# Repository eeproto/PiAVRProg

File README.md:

# Standalone AVR Programmer
Raspberry Pi based standalone ZIF Socket AVR Programmer

Program AVR chips with one click of a button:

Project Home Page: [https://eeproto.com/portfolio/avr-programmer/](https://eeproto.com/portfolio/avr-programmer/)

# Purpose

You designed a piece of hardware around an [AVR](https://en.wikipedia.org/wiki/AVR_microcontrollers) microcontroller, maybe the popular [ATmega328](https://www.microchip.com/wwwproducts/en/ATmega328). I love this powerful and inexpensive chip. Many projects use it, maybe because it is also the core of the even more popular [Arduino UNO](https://www.arduino.cc/en/Guide/ArduinoUno).

If you produce your new design two or three times, you flash your AVRs straight from your workstation. If you make 1,000, your distributor will gladly flash them for you. But what if you want, say, 50?

This project gives you all the parts to make a standalone, easy to use AVR programmer. It is Open Source, released under [Creative Commons Attribution-ShareAlike 4.0 International License](http://creativecommons.org/licenses/by-sa/4.0/), and it borrows from many other Open Source designs, including Sparkfun's [Pi AVR Programmer HAT](https://www.sparkfun.com/products/14747).

Hardware and software were tested with ATmega168 and ATmega328 chips. Feel free to adapt it to other AVR chips that support SPI programming.

# Make It

To make your own, get a Rasperry Pi. Any version should work, I tested it with a Pi 2 Model B v.1.1.

Make the custom PCB that connects the AVR socket, buttons, LEDs, etc. to the Pi.

Use the [KiCad](https://www.kicad-pcb.org/) project in the `hardware` folder to order your board. I got some from a low-cost PCB shop along with a stencil. It is a two-layer board with surface mount components on one side. There is a set of Gerber and drill files in the `hardware/plots` folder. The BOM in the same folder uses pretty generic components. The [octopart BOM](https://octopart.com/bom-tool/K1k6iRbx) might still be up.

Populate the surface mount components first. I use solder past, a stencil, tweezers, and a [ReflowR](http://www.reflowr.com/index.html) by [Lafras H](https://www.tindie.com/stores/LafrasH/). There are many other ways to do that, including hand soldering or reflowing with hot air like in this [EEVblog video](https://www.youtube.com/watch).

The 28 pin ZIF sockets can be a little hard to get, the major distributors might not have them in stock. Generic sockets through ama*** worked, too. Just make sure you get 28 pins in two rows with a 7.62mm / 0.3in row spacing.

If you don't feel comfortable with all of that, [email me](mailto:hello@eeproto.com), maybe I have some left over.

Add the through-hole parts. Double check you did not make any inadvertent solder bridges, then plug it in.

Support the PCB on top of your Pi with Nylon hex standoffs and secure everything with M3 screws.

Install the software by following the [Installation Guide](Installation.md).

# Prepare It

In order to program the AVR, you need two things:

1. A compiled HEX flash file.
2. The device configuration.

## 1. HEX file

Write and test your AVR firmware as usual. You can use [PlatformIO](https://platformio.org/), the [Arduino IDE](https://www.arduino.cc/en/Main/Software), a straight `avr-gcc` toolchain, or any other way. Build your project. 

Find the compiled HEX file. For Platform IO, look for a file `firmware.hex` in a folder `.pio/build/uno` underneath your project directory.

Copy this file to the root of a USB drive and name it `firmware.hex`. A standard FAT32 formatted drive works fine.

## 2. Device Configuration

Create a JSON file called `device.json` next to the HEX file on the USB drive. You can use the file from the `samples` folder as a starting point.

Adjust the AVR fuse settings to your needs. Here are a few samples:

| Fuses  | Settings |
|---|---|
| (E:FF, H:D9, L:E2) |Internal 8 MHz oscillator|
| (E:FF, H:D9, L:62) |Internal 1 MHz oscillator|
| (E:FD, H:DE, L:FF) | External 16 MHz crystal|
| (E:FD, H:DE, L:FF) | default Arduino UNO settings |

Set the chip type so avrdude knows what signature to expect. Common types:

|Type|Signature|
|---|---|
|atmega168|1e9406|
|atmega168p|1e940b|
|atmega168pb|1e9415|
|atmega328|1e9514|
|atmega328p|1e950f|
|atmega328pb|1e9516|

Check this [post](https://www.avrfreaks.net/forum/device-signatures) for a full list.

Example configuration file:
```json device.json
{
  "E": "FF",
  "H": "D9",
  "L": "E2",
  "type": "atmega328p"
}
```

# Use It

1. [Assemble](#make-it) the hardware and [install](Installation.md) the Pi firmware.
1. [Prepare](#prepare-it) the USB flash drive with your hex file and device configuration.
1. Power the Pi.
1. You should see the `Power` LED turn on.
1. The `Ready` LED is flashing until a USB drive with a valid device configuration and hex file is plugged in. Plug it in and wait for the `Ready` LED to turn solid green.
1. Insert an AVR chip that matches your device configuration into the ZIF socket and lock the socket. The index notch is at the top next to the title print.
1. Press the `Go!` button.
1. The `Active` LED turns on.
1. If the device needs updated fuse settings, the `Fuses Pass` LED should go green after a moment.
1. The `Flash Pass` LED goes green once flashing was successful.
1. If at any time a `Fail` LED starts flashing, the programmer was unsuccessful communicating with the AVR chip. Check everything is wired correctly and the AVR is secure in its place with Pin 1 at the top. Try a different AVR chip. If this problem continues to exist, try reducing the programming bitclock in the Python script. 

# How It Works

The Pi runs a small Linux OS based on PipaOS. On boot, it starts a Python script as a background system service.

This script reads the USB drive, looking for both a flash HEX file and a device configuration JSON file. 

If both are there, the script starts monitoring the big pushbutton labeled `Go!`.

When you press the button, the script runs avrdude to first check the device signature. Then, it reads the fuses. If they need to be programmed, it does that. Last, it writes the HEX file contents to the AVR flash memory.

Looking at the output of the avrdude commands, the script lights the LEDs to tell you what worked and what did not.

You can pull power from the Pi without shutting it down, because PipaOS allows the SD card to be mounted read-only.

The custom PCB mainly connects the SPI lines provided by the Pi to the AVR. A 4066 isolates the two chips when not programming, as the AVR might go into SPI master mode after releasing the RESET line. One momentary push button with a little ESD protection starts the programming, another one allows a clean shutdown of the Pi, in case you decide to run with a different OS setup.

To connect the AVR, you can use any standard socket, although a ZIF socket allows for frustration free insert and removal.

Although it looks like a HAT, technically this is not a HAT according to the [HAT Design Guide](https://github.com/raspberrypi/hats/blob/master/designguide.md). It still fits nicely on top of the Pi.

# Known Issues

For reasons I don't know, my prototype assemblies would only flash at a bitrate of around 200 kHz. A dirty breadboard assembly ran up to 2MHz. Need to figure out why that is.

# Credits

This project depends heavily on other people's great open source work, including:

- The [PipaOS](http://pipaos.mitako.eu/) Linux distribution by Albert Casals
- [avrdude](http://savannah.nongnu.org/projects/avrdude/) AVR programmer
- Kevin's [linuxspi](http://kevincuzner.com/2013/05/27/raspberry-pi-as-an-avr-programmer/) extension for avrdude
- Steve's [programmer design](https://blog.stevemarple.co.uk/2012/07/avrarduino-isp-programmer-using.html) with 74LVC244 isolating buffers
- adafruit's [linuxgpio-based design](https://learn.adafruit.com/program-an-avr-or-arduino-using-raspberry-pi-gpio-pins?view=all)
- Mark Williams shows how to operate the Pi [with the Arduino IDE](http://ozzmaker.com/program-avr-using-raspberry-pi-gpio/)
- QCPete's [writeup](https://learn.sparkfun.com/tutorials/raspberry-pi-stand-alone-programmer/all) on the design of the [Pi AVR Programmer HAT](https://www.sparkfun.com/products/14747)
- Volker Urban's [Pi/AVR summary](https://www.mikrocontroller.net/articles/Raspberry_Pi_als_Universalprogrammer) (german)
- [KiCad](https://www.kicad-pcb.org/), an exceptional and Open Source electronics design software
- Chris Gammell's [Contextual Electronics Forum](https://forum.contextualelectronics.com/) as an endless source of great knowledge.

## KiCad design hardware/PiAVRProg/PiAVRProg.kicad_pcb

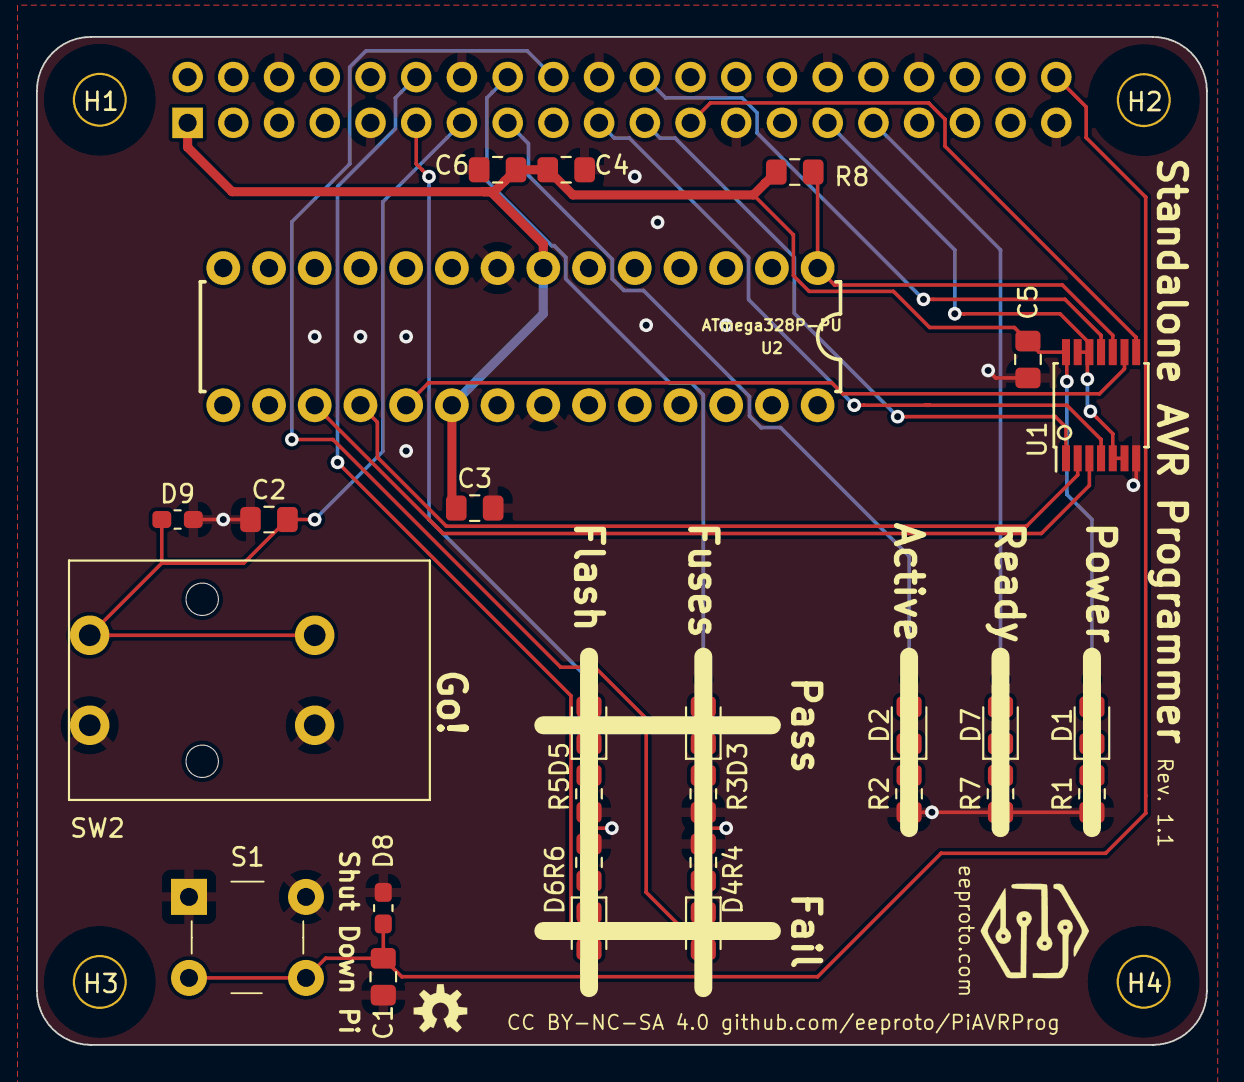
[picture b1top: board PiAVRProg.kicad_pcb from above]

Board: 2 copper layers, 65.0 x 56.0 mm, 32 parts (1 on the bottom side), 26 nets.

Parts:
C1, C2, C3, C4, C5: 0.1uF; C_0805_2012Metric_Pad1.15x1.40mm_HandSolder
C6: 10uF; C_0805_2012Metric_Pad1.15x1.40mm_HandSolder
D1, D3, D5, D7: GREEN; LED_0805_2012Metric_Pad1.15x1.40mm_HandSolder
D2: YELLOW; LED_0805_2012Metric_Pad1.15x1.40mm_HandSolder
D4, D6: RED; LED_0805_2012Metric_Pad1.15x1.40mm_HandSolder
D8, D9: D_TVS; R_0603_1608Metric_Pad1.05x0.95mm_HandSolder
H1, H2, H3, H4: 3mm_Mounting_Hole; NPTH_3mm_ID
J1: 40HAT; PinSocket_2x20_P2.54mm_Vertical
R1, R2, R3, R4, R5, R6, R7: 1k; R_0805_2012Metric_Pad1.15x1.40mm_HandSolder
R8: 10k; R_0805_2012Metric_Pad1.15x1.40mm_HandSolder
S1: B3F-1000; Switch_Tactile_THT_B3F-1xxx
SW2: MOM; OmronB3J1100
U1: 4066; TSSOP-14_4.4x5mm_P0.65mm
U2: ATmega328P-PU; DIL28-3-ZIF_SOCKET

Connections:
+3V3: C3.1, C4.1, C5.1, C6.1, D1.2, J1.1, R8.1, U1.14, U2.7, U2.20
/AVR_CLK: U1.9, U2.19
/AVR_MISO: U1.2, U2.18
/AVR_MOSI: U1.3, U2.17
/AVR_RESET: R8.2, U1.10, U2.1
/FLASH_FAIL: D6.2, J1.12
/FLASH_PASS: D5.2, J1.11
/FUSE_FAIL: D4.2, J1.18
/FUSE_PASS: D3.2, J1.16
/PI_CLK: J1.23, U1.8
/PI_GO: C2.2, D9.1, J1.13, SW2.1
/PI_MISO: J1.21, U1.1
/PI_MOSI: J1.19, U1.4
/PI_RESET: J1.22, U1.11
/PI_SHUTDOWN: C1.2, D8.1, J1.40, S1.3, S1.4
/PROGRAMMING: D2.2, J1.15
/READY: D7.2, J1.31
/SPI_SWITCH: J1.29, U1.5, U1.6, U1.12, U1.13
GND: C1.1, C2.1, C3.2, C4.2, C5.2, C6.2, D8.2, D9.2, J1.6, J1.9, J1.14, J1.20, J1.25, J1.30, J1.34, J1.39, R1.1, R2.1, R3.1, R4.1, R5.1, R6.1, R7.1, S1.1, S1.2, SW2.2, U1.7, U2.8, U2.22
unnamed: D1.1, R1.2
unnamed: D2.1, R2.2
unnamed: D3.1, R3.2
unnamed: D4.1, R4.2
unnamed: D5.1, R5.2
unnamed: D6.1, R6.2
unnamed: D7.1, R7.2

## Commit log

2020-01-06 initial github commit
2020-01-17 limit info output when idle
2020-01-21 pin 1 indicator
2024-10-04 kicad 8

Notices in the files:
hardware/PiAVRProg/PiAVRProg.kicad_pcb:
License: This work is licensed under CC BY-NC-SA 4.0
CC BY-NC-SA 4.0 github.com/eeproto/PiAVRProg
